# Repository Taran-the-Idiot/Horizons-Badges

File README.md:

# Horizons Crux Badges

E-ink badges for Horizons Crux! Made in Kicad. They use 2.66" E-ink screens with an RP2040 mcu. And they are made in the shape of a mantaray :D

Just use a piece of double sided tape to secure down the screen and you are good to go!

Features: 

- usbC connector
- 2.66" E-ink
- No battery required
- Has a lanyard hole

## Schematic

Here is the schematic for this board. It is a normal rp2040 microcontroller with an E-ink driver integrated into it. 

## PCB

Here is the pcb layout and design. This is a 2 layer board that has a ground pour, as well as a 3v3 pour on the top side over where the mcu electronics are. 

The files for the individual art sections can be found labelled in the [/art](/art) directory.

### Art

The art was drawn by [@variidian](https://github.com/variidian). The original art files and the vectorised sections for pcb production can be found in the [/art](/art) folder. 

## Firmware

The badge can be flashed using the [Badge Paint Website](https://badge-paint.notaroomba.dev/).

You draw what you want or load in the preset and fill in the details. you then need to flash a micropython .uf2 and it will then allow you to flash the badge.

This site was made by [@notaroomba](https://github.com/notaroomba)

#### Credits

Credit to [@variidian](https://github.com/variidian) for making the art for the badge and credit to [@notaroomba](https://github.com/notaroomba) for writing the software.

Also a thank you to [JLCPCB](https://jlcpcb.com) for sponsoring the badges!

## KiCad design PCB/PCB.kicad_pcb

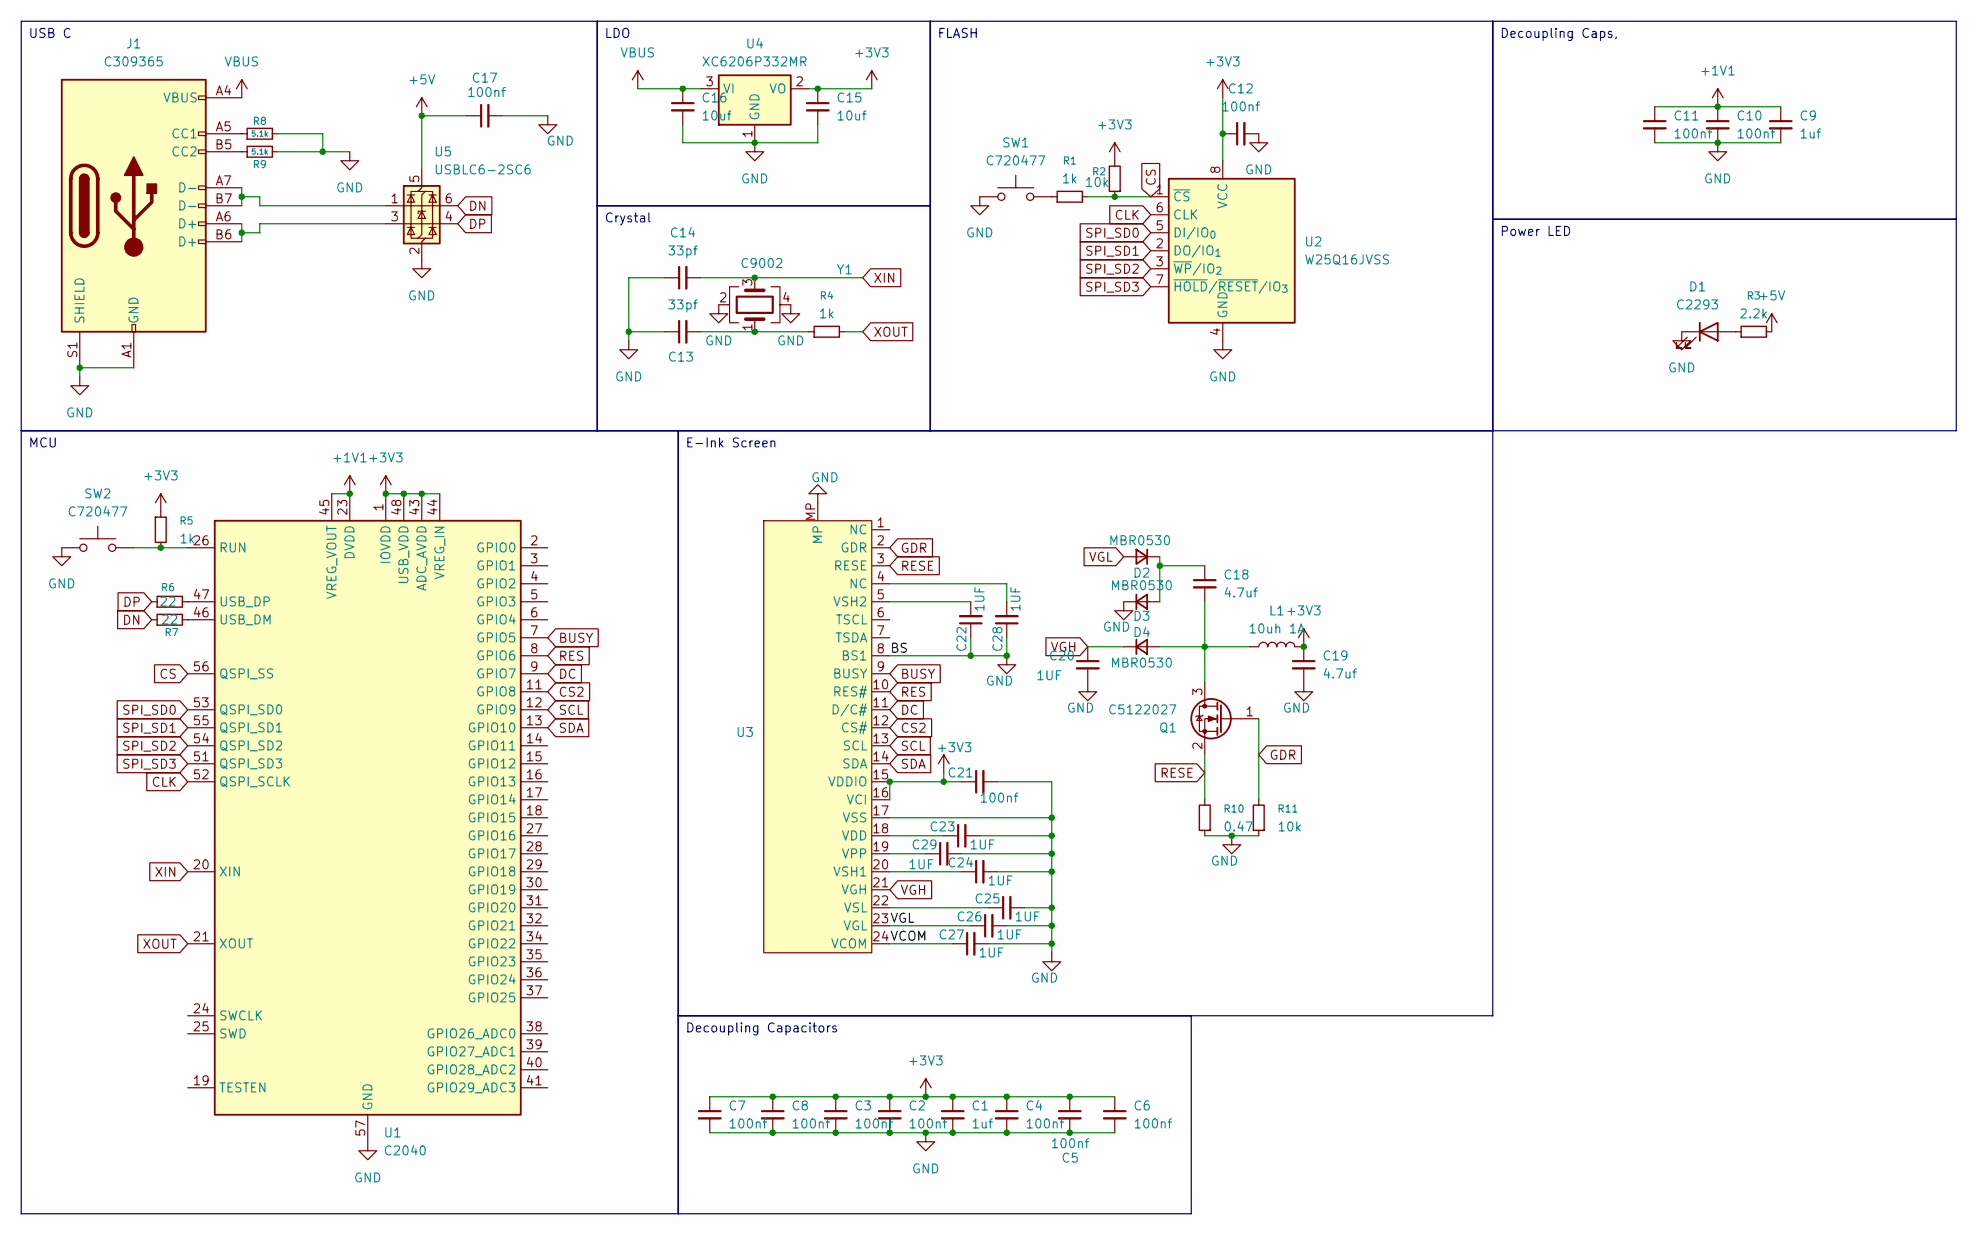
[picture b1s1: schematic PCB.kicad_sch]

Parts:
C1, C9: 1uf; C_0402_1005Metric
C2, C3, C4, C5, C6, C7, C8, C10, C11, C12, C17, C21: 100nf; C_0402_1005Metric
C13, C14: 33pf; C_0603_1608Metric
C15, C16: 10uf; C_0603_1608Metric
C18, C19: 4.7uf; C_0402_1005Metric
C20, C22, C23, C24, C25, C26, C27, C28, C29: 1UF; C_0402_1005Metric
D1: C2293; LED_0805_2012Metric
D2, D3, D4: MBR0530; SOD-123_L2.8-W1.8-LS3.7-RD
J1: C309365; USB-C-SMD_20P-P0.50-L6.5-W8.9
L1: 10uh 1A; IND-SMD_L4.0-W4.0_FNR40XXS
Q1: C5122027; SOT-23
R1, R4, R5: 1k; R_0402_1005Metric
R2: 10k; R_0402_1005Metric
R3: 2.2k; R_0402_1005Metric
R6, R7: 22; R_0402_1005Metric
R8, R9: 5.1k; R_0402_1005Metric
R10: 0.47; R_0402_1005Metric
R11: 10k; R_0603_1608Metric
SW1, SW2: C720477
U1: C2040; QFN-56-1EP_7x7mm_P0.4mm_EP3.2x3.2mm_ThermalVias
U2: W25Q16JVSS; SOIC-8_5.3x5.3mm_P1.27mm
U3: FPC-SMD_24P-P0.50_05A20L24P
U4: XC6206P332MR; SOT-23
U5: USBLC6-2SC6; SOT-23-6
Y1: C9002; CRYSTAL-SMD_4P-L3.2-W2.5-BL

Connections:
+1V1: C9.1, C10.1, C11.1, U1.23 (DVDD), U1.45 (VREG_VOUT), U1.50 (DVDD)
+3V3: C1.1, C2.1, C3.1, C4.1, C5.1, C6.1, C7.1, C8.1, C12.1, C15.1, C19.1, C21.1, L1.2, R2.2, R5.1, U1.1 (IOVDD), U1.10 (IOVDD), U1.22 (IOVDD), U1.33 (IOVDD), U1.42 (IOVDD), U1.43 (ADC_AVDD), U1.44 (VREG_IN), U1.48 (USB_VDD), U1.49 (IOVDD), U2.8 (VCC), U3.15 (VDDIO), U3.16 (VCI), U4.2 (VO)
+5V: C17.1, R3.2, U5.5 (VBUS)
/VCOM: C27.1, U3.24 (VCOM)
BUSY: U1.7 (GPIO5), U3.9 (BUSY)
CLK: U1.52 (QSPI_SCLK), U2.6 (CLK)
CS: R1.2, R2.1, U1.56 (QSPI_SS), U2.1 (~CS)
CS2: U1.11 (GPIO8), U3.12 (CS#)
DC: U1.9 (GPIO7), U3.11 (D/C#)
DN: R7.1, U5.6 (I/O1)
DP: R6.1, U5.4 (I/O2)
GDR: Q1.1 (G), R11.2, U3.2 (GDR)
GND: C1.2, C2.2, C3.2, C4.2, C5.2, C6.2, C7.2, C8.2, C9.2, C10.2, C11.2, C12.2, C13.1, C14.1, C15.2, C16.2, C17.2, C19.2, C20.2, C21.2, C22.1, C23.2, C24.2, C25.2, C26.2, C27.2, C28.1, C29.2, D1.1 (K), D3.1 (K), J1.A1 (GND), J1.A12 (GND), J1.B1 (GND), J1.B12 (GND), J1.S1 (SHIELD), R8.2, R9.2, R10.1, R11.1, SW1.1, SW2.1, U1.57 (GND), U2.4 (GND), U3.8 (BS1), U3.17 (VSS), U3.MP, U4.1 (GND), U5.2 (GND), Y1.2, Y1.4
unnamed: C13.2, R4.1, Y1.1
unnamed: C28.2, U3.4 (NC)
unnamed: D1.2 (A), R3.1
unnamed: C18.1, D2.1 (K), D3.2 (A)
unnamed: C18.2, D4.2 (A), L1.1, Q1.3 (D)
unnamed: J1.A5 (CC1), R8.1
unnamed: J1.B5 (CC2), R9.1
unnamed: J1.A6 (D+), J1.B6 (D+), U5.3 (I/O2)
unnamed: J1.A7 (D-), J1.B7 (D-), U5.1 (I/O1)
unnamed: R1.1, SW1.2
unnamed: R5.2, SW2.2, U1.26 (RUN)
unnamed: R7.2, U1.46 (USB_DM)
unnamed: R6.2, U1.47 (USB_DP)
unnamed: C23.1, U3.18 (VDD)
unnamed: C29.1, U3.19 (VPP)
unnamed: C24.1, U3.20 (VSH1)
unnamed: C22.2, U3.5 (VSH2)
unnamed: C25.1, U3.22 (VSL)
RES: U1.8 (GPIO6), U3.10 (RES#)
RESE: Q1.2 (S), R10.2, U3.3 (RESE)
SCL: U1.12 (GPIO9), U3.13 (SCL)
SDA: U1.13 (GPIO10), U3.14 (SDA)
SPI_SD0: U1.53 (QSPI_SD0), U2.5 (DI/IO_{0})
SPI_SD1: U1.55 (QSPI_SD1), U2.2 (DO/IO_{1})
SPI_SD2: U1.54 (QSPI_SD2), U2.3 (~WP/IO_{2})
SPI_SD3: U1.51 (QSPI_SD3), U2.7 (~HOLD/~RESET/IO_{3})
VBUS: C16.1, J1.A4 (VBUS), J1.A9 (VBUS), J1.B4 (VBUS), J1.B9 (VBUS), U4.3 (VI)
VGH: C20.1, D4.1 (K), U3.21 (VGH)
VGL: C26.1, D2.2 (A), U3.23 (VGL)
XIN: C14.2, U1.20 (XIN), Y1.3
XOUT: R4.2, U1.21 (XOUT)

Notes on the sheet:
USB C
Crystal
Decoupling Capacitors
FLASH
MCU
E-Ink Screen
LDO
Decoupling Caps,
Power LED

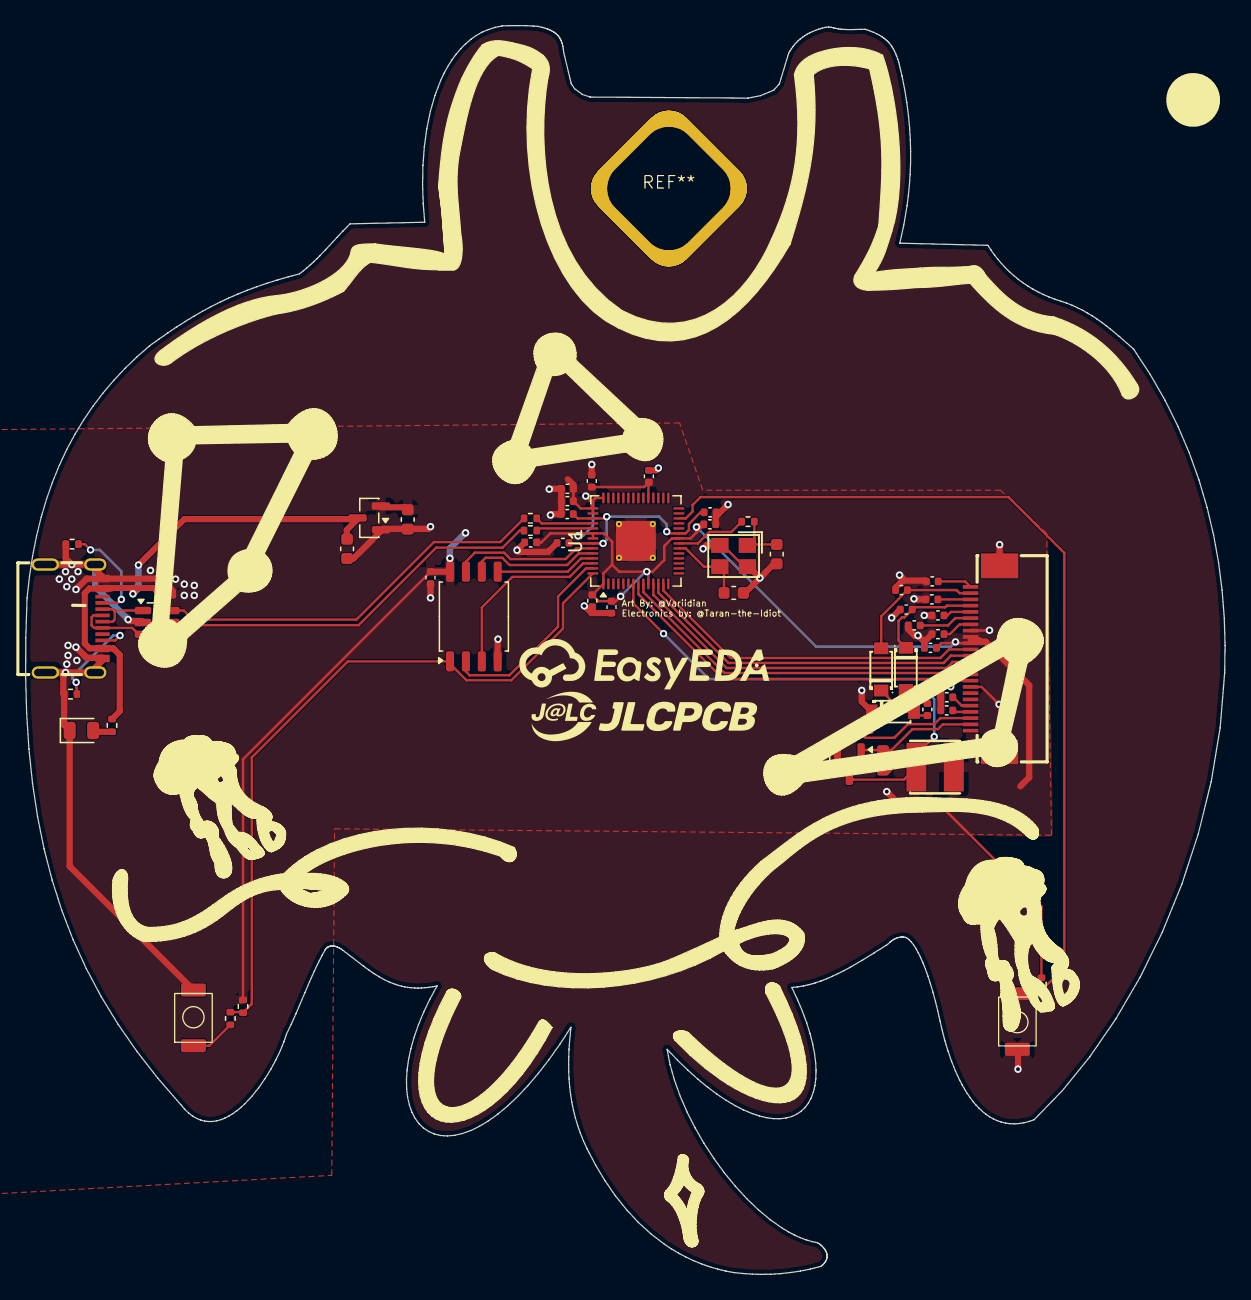
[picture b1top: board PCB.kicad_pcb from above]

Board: 2 copper layers, 96.0 x 99.9 mm, 55 parts (0 on the bottom side), 44 nets.

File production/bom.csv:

Designator,Footprint,Quantity,Value,LCSC Part #
"C1, C20, C22, C23, C24, C25, C26, C27, C28, C29, C9",0402,11,1uf,
"C10, C11, C12, C17, C2, C21, C3, C4, C5, C6, C7, C8",0402,12,100nf,
"C13, C14",0603,2,33pf,
"C15, C16",0603,2,10uf,
"C18, C19",0402,2,4.7uf,
D1,0805,1,C2293,
"D2, D3, D4",SOD-123_L2.8-W1.8-LS3.7-RD,3,MBR0530,
J1,USB-C-SMD_20P-P0.50-L6.5-W8.9,1,C309365,
L1,IND-SMD_L4.0-W4.0_FNR40XXS,1,10uh 1A,
Q1,SOT-23,1,C5122027,
"R1, R4, R5",0402,3,1k,
R10,0402,1,0.47,
R11,0603,1,10k,
R2,0402,1,10k,
R3,0402,1,2.2k,
"R6, R7",0402,2,22,
"R8, R9",0402,2,5.1k,
"SW1, SW2",C720477,2,C720477,
U1,QFN-56-1EP_7x7mm_P0.4mm_EP3.2x3.2mm_ThermalVias,1,C2040,
U2,SOIC-8_5.3x5.3mm_P1.27mm,1,W25Q16JVSS,
U3,FPC-SMD_24P-P0.50_05A20L24P,1,~,
U4,SOT-23,1,XC6206P332MR,
U5,SOT-23-6,1,USBLC6-2SC6,
Y1,CRYSTAL-SMD_4P-L3.2-W2.5-BL,1,C9002,

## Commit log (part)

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2026-03-18 blehblheblhe
2026-03-18 bleh v2
2026-03-18 this feels too easy. im scared
2026-03-18 i am developing a hate of making footprints
2026-03-18 banaaaana
2026-03-19 i feel like this footprint is wrong but its not idk
2026-03-19 everything is fine
2026-03-19 routing is fun
2026-03-19 amongus vias arent real, they cant hurt you. amongus vias:
2026-03-19 descriptive commit name
2026-03-19 push
2026-03-19 potato
2026-03-19 lanyard hole
2026-03-20 remove .csv files from stinky gitignore
    Remove BOM file patterns from .gitignore
2026-03-20 more stinky gitignore stuff
2026-03-20 why wont the gitignore work
2026-04-02 now its time to open vscode for the first time in months
2026-04-02 bleh
2026-04-02 blah bleh
2026-04-02 83 error tags :D
2026-04-02 new prod stuff
2026-04-02 stinky models
2026-04-02 commit arson
2026-04-02 FINISHED(minus the readme)
2026-04-02 gitignore please work this time
2026-05-31 comit
2026-06-05 commit beeg stuff(i forgor to commit for a while)
2026-06-06 banana
2026-06-06 journal 1
2026-06-06 more journal
2026-06-09 Cleanup Schematic
2026-06-11 anything except engineering
2026-06-11 huzzah
